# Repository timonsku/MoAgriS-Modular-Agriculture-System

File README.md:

# MoAgriS - Modular Agriculture System

## Introduction
MoAgriS is a System to automate plant care with the help of modules for light, water and wind. The modules are plugged onto 3 rods providing power and communication. This way they can be placed individually to fit the plants needs. The project has been developed under Windows but the use of Linux is possible and encouraged.

## Quickstart
There is none. You need to get the PCBs and the components of the [BOM](#bom) first and combine them yourself or let your provider populate everything. [LCSC](https://lcsc.com/) has been quite usefull since they offer a [PCB service](https://jlcpcb.com/) besides the components and the shipment can be combined. A possible PCB configuration can be seen in [PCB/notes/pcb-spec.PNG](./PCB/notes/pcb-spec.PNG). The default values such as PCB thickness or copper weight of 1 oz are fine, too. Unfortunately not all parts can be found there at the time of writing such as the SAMD11 or the PT4115 current regulator.

Once a PCB is ready the SAMD11 needs a [bootloader](https://github.com/mattairtech/ArduinoCore-samd/blob/master/bootloaders/zero/binaries/sam_ba_Generic_D11C14A_SAMD11C14A.bin) by [Mattairtech](https://github.com/mattairtech) to be transmitted via the SWD interface. This is a one-time procedure since the bootloader handles all the firmware updates via USB afterwards. The [Segger J-Link](https://www.segger.com/products/debug-probes/j-link/models/j-link-edu-mini/) comes in handy for that if the licensing is not a problem to you. Other solutions are possible as long as the SAMD11 is supported. Currently I use [Atmel Studio](https://www.microchip.com/mplab/avr-support/atmel-studio-7) for this step (Tools->Device Programming) though the Studio is quite an overkill.

Right now there is no Firmware binary (see [Future](#Future)) so you need to go through the [Development](#Development) section to set up the [Arduino IDE](https://www.arduino.cc/en/main/software). After that you can compile and upload the firmwares found in [Firmware](/Firmware). You need one master on the SDI bus and you can use pretty much as many slaves as you want - tell me if there's a limit. The master can be any PCB that has a SAMD11 if you wish to wish keep your order small. The dedicated master PCB only has power and BUS connectors.

Now that the PCBs are fully working it's time to clamp them on the rods. Plug the master via USB into your PC/Raspberry and open a serial console such as Realterm (Windows) or minicom (Linux). Find out the masters COM-Port (Windows: Device Manager -> COM & LPT ports -> the one thats containing Mattairtech in the description), set the Baud rate to 115200 and connect to it. You should receive a welcoming "Opening SDI-12 bus master..." the first time you connect to the master. It's best to tell your terminal to add a line feed (\n) to a command. This way the master knows to send it over the SDI bus - it's not neccessary since a command is sent anyway after a timeout of 1s.

That's it pretty much. You should be able to send commands to the individual modules now. There's a node-red solution in development to automate it further.

## Development
Thanks to [Mattairtechs ArduinoCore-samd](https://github.com/mattairtech/ArduinoCore-samd) firmware development is quite easy. The setup is described [here](https://github.com/mattairtech/ArduinoCore-samd#installation) (two parts!). The flash size of the SAMD11 is quite small to fit in all the firmware but it is possible if you turn off as many functions as possible in the config.h (Windows: C:\Users\User\AppData\Local\Arduino15\packages\MattairTech_Arduino\hardware\samd\1.6.18-beta-b1\config.h). My config can be found in [Firmware/config.h](./Firmware/config.h). Additionally you should avoid costful code such as the String datatype. Right now the complete firmware for the slave takes up 10232 Bytes.

## SDI Commands
The SDI protocol consists of commands from the master and answers from the sensors in printable 7bit ACII characters. A command starts with an [address](#Addressing) followed by an instruction and an optional parameter. It is finished with an '!' and sent to the module(s). If the command is a heartbeat or a group instruction the module doesn't answer. If a certain module is addressed the answer will be given via the SDI bus starting with its address and an answer. That string is also printed to the serial if you connected the module via USB for debugging purposes.

### Addressing
The modules are addressed by a 4 character lower case hex string which represents two bytes of an SDI address. It is created during bootup in the module by xoring the 3 serial number registers of the SAMD11. Since there is no EEPROM on the controller this seems to be the best solution for getting almost unique addresses. When you install the firmware you should set up a one master one slave system to get the modules address by '?I!' and write it somewhere like the left out rectangle on the module.

Besides addressing a single module you can address multiple ones with a single command. That way you won't receive an answer though. The wildcard character '?' will address all modules. If an single upper case letter is used you can address groups. The default group is 'N' as in None. You can set the group of a module by sending 'abcdGL!' ('abcd' = address, 'G' = set group, 'L' = Group L). Remember there is no EEPROM so the group will be lost once the module reboots. Either write a setup routine or set SDIGROUPDEFAULT in the firmware code to keep the group after booting.

### Instructions
Commands should be finished with \n and responses are finished by \r\n by the module itself.

| Instruction | Description | Answer | Example (Command!Response) |
| ----------- | ----------- | ------ | -------------------------- |
| I | Identification | abcd | ?I!abcd |
|||(Address)||
| V | Version | 00.00.02 | abcdV!abcd00.00.02 |
|||(Version)||
| Ccccc | Change address | [new Address] | abcdC1234!1234 |
|| cccc: Address |||
| H | Send Heartbeat to avoid module returning to a save state| - | ?H! |
| Jiiii | Set heartbeat interval | ACK | abcdJ0060!abcdACK |
|| iiii .. Interval in seconds (trailing 0s)
| Gc | Set SDI group | ACK | abcdGL!abcdACK
|| c: Group
| K | Get SDI group | [Group] | abcdK!abcdL
| Si | Set status LED | ACK | abcdS0!abcdACK
|| i: 0 (on), 1 (off) 
| Liii | Set power LED | ACK | abcdL100!abcdACK
|| iii: 000..255 (trailing 0s) || LL255!
| Pi | Set pump | ACK | abcdP1
|| i: 1(on), 0(off)
| Fiii | Set fan | ACK | abcdF100!abcdACK
|| iii: 000..255 (trailing 0s)

## BOM
The [BOM /PCB/notes/BOM.ods](./PCB/notes/BOM.ods) is divided into the BaseBoard which contains the components all modules share except for the Angle. Since some more parts of the BaseBoard are required for certain modules the column "See also" tells you where to look. 
There is also a [Accessories /PCB/notes/Accessories.ods](./PCB/notes/Accessories.ods) list to find some ideas about the other utensils.

## Modules
All modules are created in [Eagle](https://www.autodesk.com/products/eagle/overview) and are within the 10cm*10cm limit to use the free version.

### LED-Module 
Provides light by 3 full spectrum LEDs which intensity can be controlled via SDI. The long version has a better light and heat distribution.

### Pump-Module 
Provides water by a pump by switching it on/off via SDI. 

### Fan-Module
Provides wind by a fan that can be controlled via PWM over SDI. 

### SDI-Master
Optional board to be used as a SDI master. You can use any other module as a master but this one is optimized for the job. It is as slim as the LED PCB and has two possible power connectors - only use one. The screw connector also has a third terminal to also chain the BUS signal.

### Angle
Provides an ~90° angle for the rods. 

## Future
More things could be added such as
- Sensors: Currently a LED-Board is technically capable of driving sensors since all pins are routed outside:
	- Watering could depend on the wetness of the soil
	- Measure the water level of the pump tank to send an alert to refill
- Create a node-red configuration
- Find an alternative to Atmel Studio for installing the bootloader
- Provide firmware binaries to avoid setting up Arduino IDE

## Bugs
- Modules don't answer after hours of no use
- Sometimes there's a voltage on the BUS of 0.1-2.5V
- Sometimes the BUS only works when a logic analyzer is attached to GND/BUS

## More
<br />This work is licensed under a <a rel="license" href="http://creativecommons.org/licenses/by-sa/4.0/">Creative Commons Attribution-ShareAlike 4.0 International License</a>.

For more details see https://hackaday.io/project/91757-moagris-modular-agriculture-system

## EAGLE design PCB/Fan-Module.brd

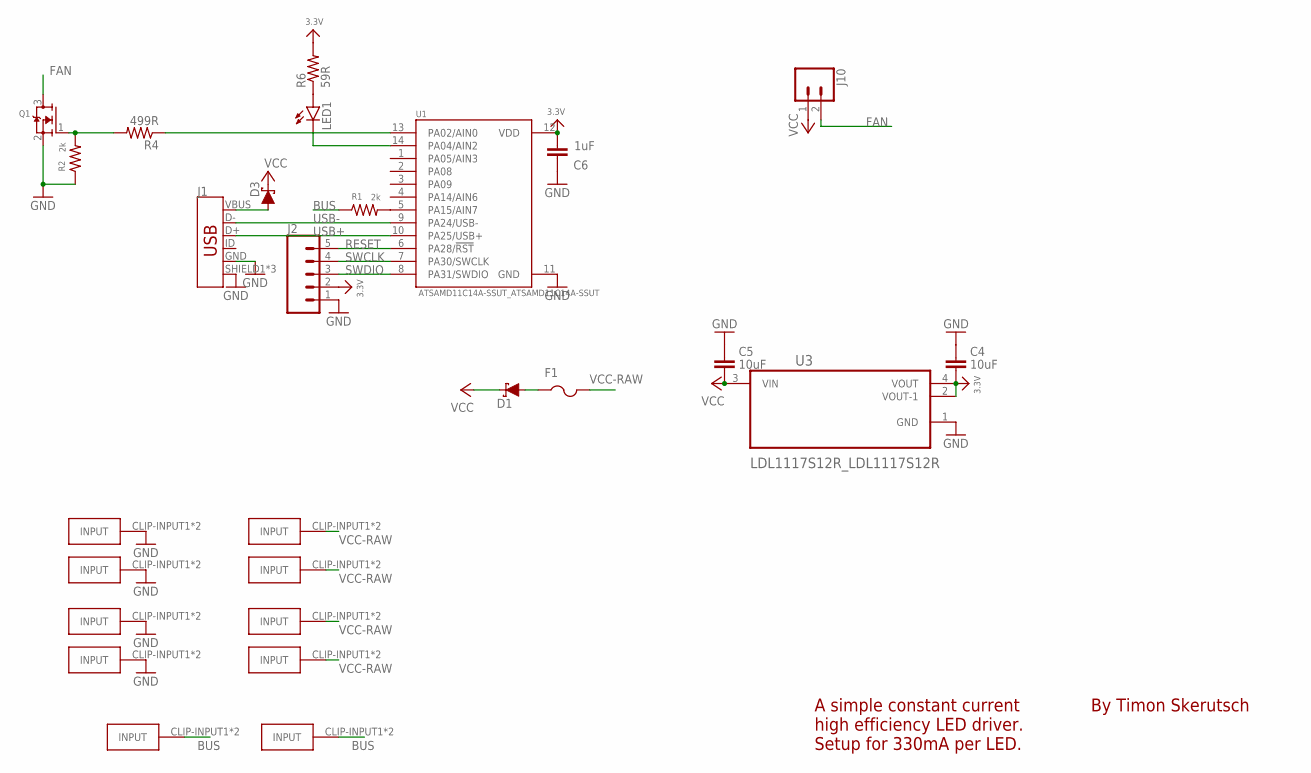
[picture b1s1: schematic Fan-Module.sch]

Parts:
C4, C5: 10uF; C0603
C6: 1uF; C0603
D1, D3: 3A/40V/500mV; SMA-DIODE
F1: PTCFUSE-1812; 1812
GND-CLIP, GND-CLIP1, GND-CLIP2, GND-CLIP3: FUSE-HOLDER-5X20MM
J1: USB_MICRO-B_FEMALE-SMT; USB-B-MICRO-SMD
J2: CONN_05; 1X05
J10: CONN_02PTH3; 1X02_LONGPADS
LED1: LEDCHIPLED_0805; CHIPLED_0805
PWM-CLIP, PWM-CLIP1: FUSE-HOLDER-5X20MM
Q1: MOSFET-NWIDE; SOT23-WIDE
R1, R2: 2k; R1206
R4: 499R; R0805
R6: 59R; R0805
U1: ATSAMD11C14A-SSUT_ATSAMD11C14A-SSUT; ATSAMD11C14A-SSUT_SOIC127P600X160-14N
U3: LDL1117S12R_LDL1117S12R; LDL1117S12R_SOT230P700X180-4N
VCC-CLIP, VCC-CLIP1, VCC-CLIP2, VCC-CLIP3: FUSE-HOLDER-5X20MM

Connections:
3.3V: C4.2, C6.2, J2.2, R6.2, U1.12 (VDD), U3.2 (VOUT-1), U3.4 (VOUT)
BUS: PWM-CLIP.CLIP-INPUT1, PWM-CLIP.CLIP-INPUT2, PWM-CLIP1.CLIP-INPUT1, PWM-CLIP1.CLIP-INPUT2, R1.1
FAN: J10.2, Q1.3 (D)
GND: C4.1, C5.1, C6.1, GND-CLIP.CLIP-INPUT1, GND-CLIP.CLIP-INPUT2, GND-CLIP1.CLIP-INPUT1, GND-CLIP1.CLIP-INPUT2, GND-CLIP2.CLIP-INPUT1, GND-CLIP2.CLIP-INPUT2, GND-CLIP3.CLIP-INPUT1, GND-CLIP3.CLIP-INPUT2, J1.GND, J1.SHIELD1 (SHIELD), J1.SHIELD2 (SHIELD), J1.SHIELD3 (SHIELD), J2.1, Q1.2 (S), R2.1, U1.11 (GND), U3.1 (GND)
unnamed: LED1.C, U1.14 (PA04/AIN2)
unnamed: LED1.A, R6.1
unnamed: R1.2, U1.5 (PA15/AIN7)
unnamed: D3.A, J1.VBUS
unnamed: R4.1, U1.13 (PA02/AIN0)
unnamed: D1.A, F1.1
unnamed: Q1.1 (G), R2.2, R4.2
RESET: J2.5, U1.6 (PA28/!RST)
SWCLK: J2.4, U1.7 (PA30/SWCLK)
SWDIO: J2.3, U1.8 (PA31/SWDIO)
USB+: J1.D+, U1.10 (PA25/USB+)
USB-: J1.D-, U1.9 (PA24/USB-)
VCC: C5.2, D1.C, D3.C, J10.1, U3.3 (VIN)
VCC-RAW: F1.2, VCC-CLIP.CLIP-INPUT1, VCC-CLIP.CLIP-INPUT2, VCC-CLIP1.CLIP-INPUT1, VCC-CLIP1.CLIP-INPUT2, VCC-CLIP2.CLIP-INPUT1, VCC-CLIP2.CLIP-INPUT2, VCC-CLIP3.CLIP-INPUT1, VCC-CLIP3.CLIP-INPUT2

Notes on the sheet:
By Timon Skerutsch
A simple constant current high efficiency LED driver. Setup for 330mA per LED.

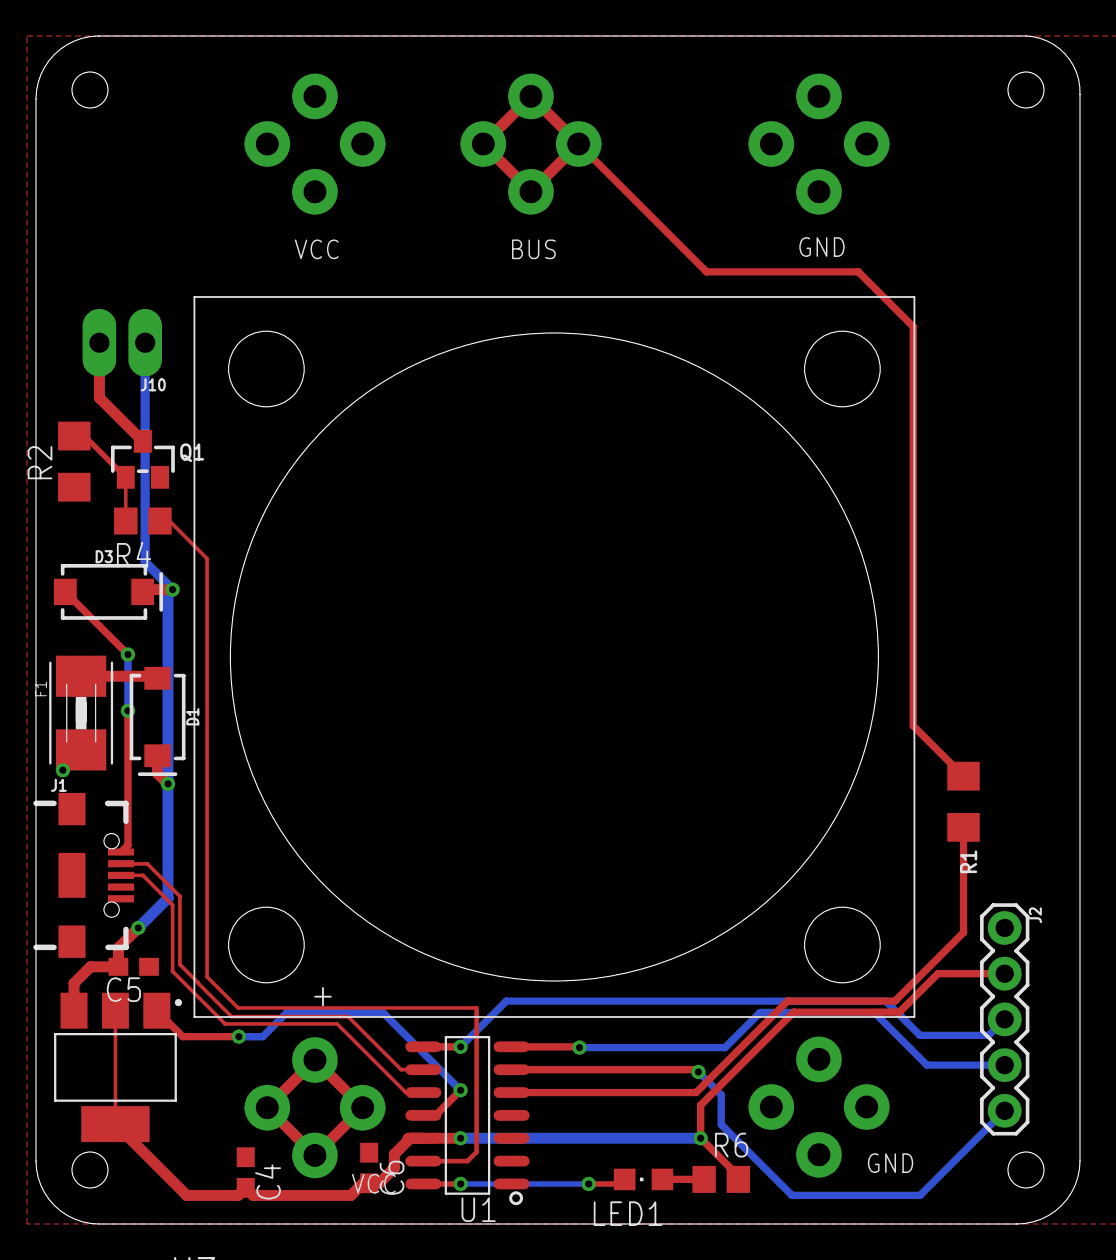
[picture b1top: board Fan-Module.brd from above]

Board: 2 copper layers, 58.0 x 66.0 mm, 28 parts (1 on the bottom side), 18 nets.

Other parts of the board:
U$1: 40MM-FAN

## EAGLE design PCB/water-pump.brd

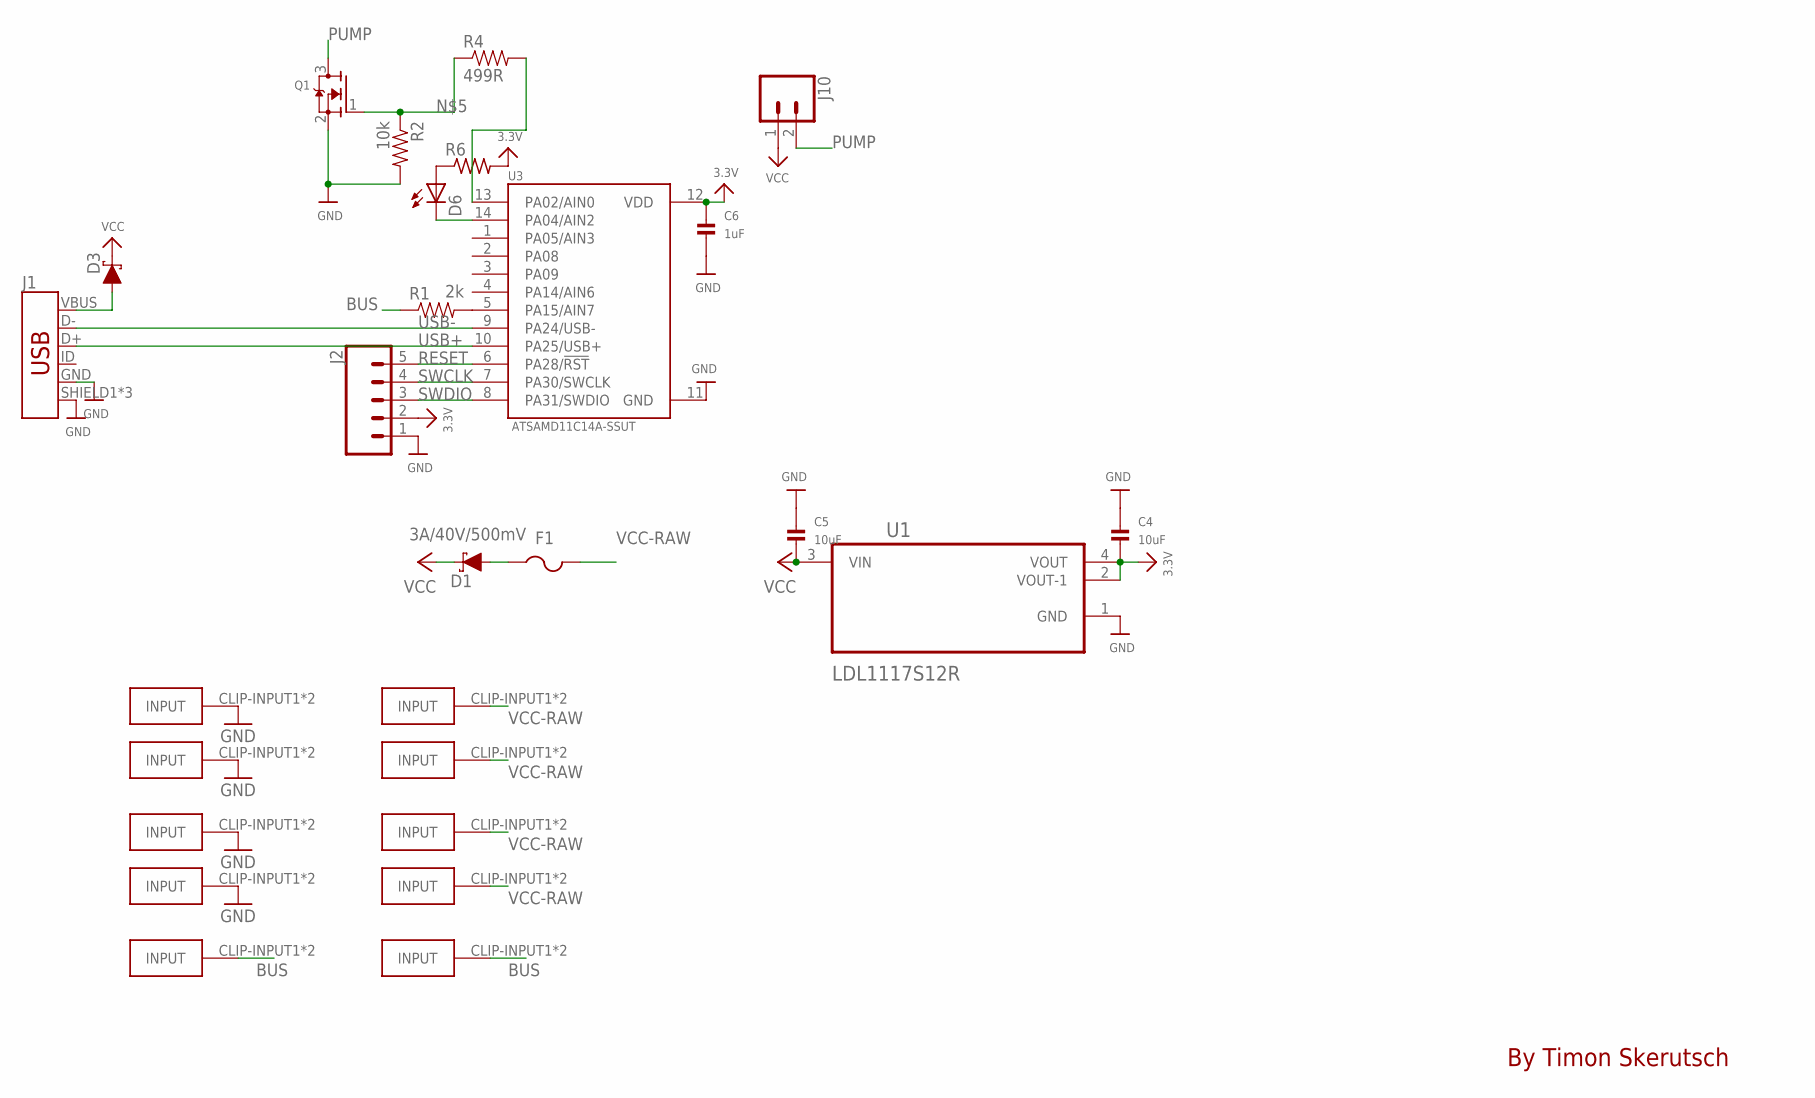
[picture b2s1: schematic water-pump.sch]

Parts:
C4, C5: 10uF; 0805
C6: 1uF; 0603
D1, D3: 3A/40V/500mV; SMA-DIODE
D6: LEDCHIPLED_0805; CHIPLED_0805
F1: PTCFUSE-1812; 1812
GND-CLIP, GND-CLIP1, GND-CLIP2, GND-CLIP3: FUSE-HOLDER-5X20MM
J1: USB_MICRO-B_FEMALE-SMT; USB-B-MICRO-SMD
J2: CONN_05; 1X05
J10: CONN_02PTH3; 1X02_LONGPADS
PWM-CLIP, PWM-CLIP1: FUSE-HOLDER-5X20MM
Q1: MOSFET-NWIDE; SOT23-WIDE
R1: 2k; 1206
R2: 10k; 1206
R4: 499R; 1206
R6: R-US_R0805; R0805
U1: LDL1117S12R; SOT230P700X180-4N
U3: ATSAMD11C14A-SSUT; SOIC127P600X160-14N
VCC-CLIP, VCC-CLIP1, VCC-CLIP2, VCC-CLIP3: FUSE-HOLDER-5X20MM

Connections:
3.3V: C4.2, C6.1, J2.2, R6.2, U1.2 (VOUT-1), U1.4 (VOUT), U3.12 (VDD)
BUS: PWM-CLIP.CLIP-INPUT1, PWM-CLIP.CLIP-INPUT2, PWM-CLIP1.CLIP-INPUT1, PWM-CLIP1.CLIP-INPUT2, R1.1
GND: C4.1, C5.1, C6.2, GND-CLIP.CLIP-INPUT1, GND-CLIP.CLIP-INPUT2, GND-CLIP1.CLIP-INPUT1, GND-CLIP1.CLIP-INPUT2, GND-CLIP2.CLIP-INPUT1, GND-CLIP2.CLIP-INPUT2, GND-CLIP3.CLIP-INPUT1, GND-CLIP3.CLIP-INPUT2, J1.GND, J1.SHIELD1 (SHIELD), J1.SHIELD2 (SHIELD), J1.SHIELD3 (SHIELD), J2.1, Q1.2 (S), R2.2, U1.1 (GND), U3.11 (GND)
unnamed: D3.A, J1.VBUS
unnamed: R1.2, U3.5 (PA15/AIN7)
unnamed: Q1.1 (G), R2.1, R4.1
unnamed: D1.A, F1.1
unnamed: D6.A, R6.1
unnamed: D6.C, U3.14 (PA04/AIN2)
PUMP: J10.2, Q1.3 (D)
PUMP_CTRL: R4.2, U3.13 (PA02/AIN0)
RESET: J2.5, U3.6 (PA28/!RST)
SWCLK: J2.4, U3.7 (PA30/SWCLK)
SWDIO: J2.3, U3.8 (PA31/SWDIO)
USB+: J1.D+, U3.10 (PA25/USB+)
USB-: J1.D-, U3.9 (PA24/USB-)
VCC: C5.2, D1.C, D3.C, J10.1, U1.3 (VIN)
VCC-RAW: F1.2, VCC-CLIP.CLIP-INPUT1, VCC-CLIP.CLIP-INPUT2, VCC-CLIP1.CLIP-INPUT1, VCC-CLIP1.CLIP-INPUT2, VCC-CLIP2.CLIP-INPUT1, VCC-CLIP2.CLIP-INPUT2, VCC-CLIP3.CLIP-INPUT1, VCC-CLIP3.CLIP-INPUT2

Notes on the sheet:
By Timon Skerutsch

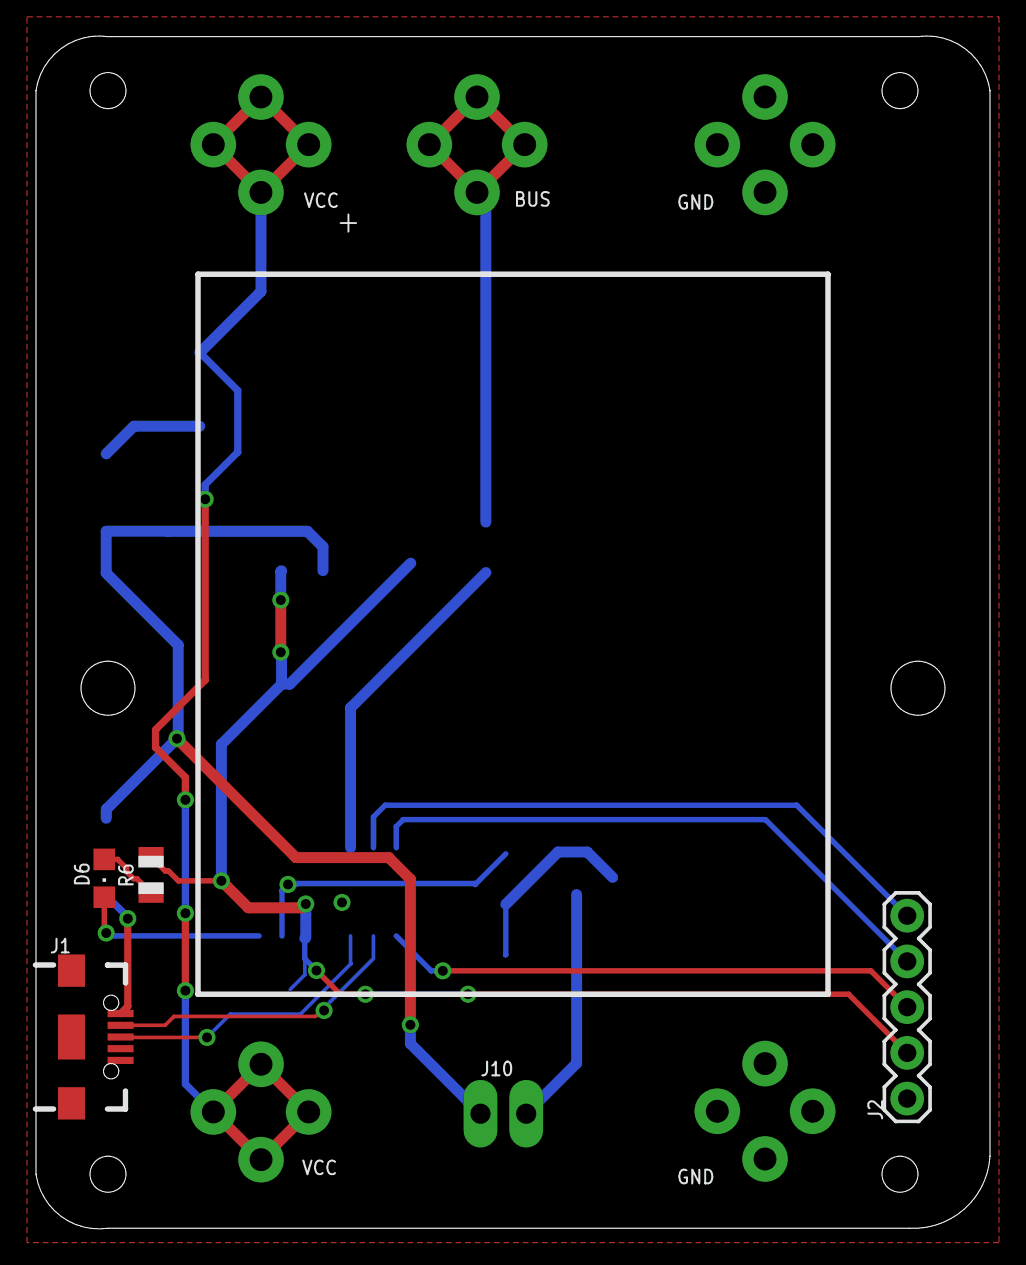
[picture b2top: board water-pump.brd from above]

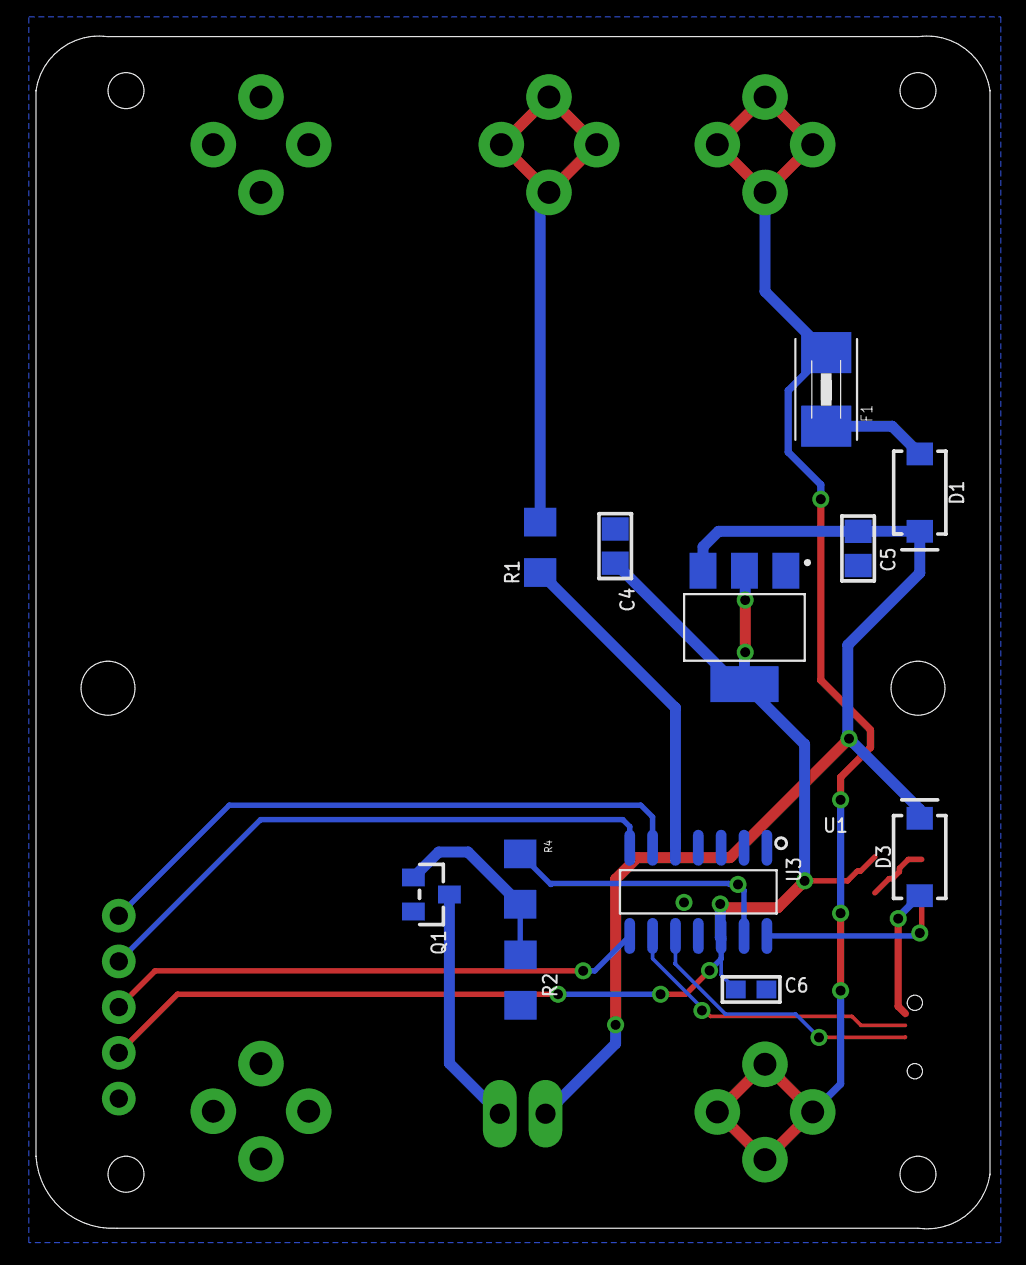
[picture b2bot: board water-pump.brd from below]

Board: 2 copper layers, 53.0 x 66.3 mm, 27 parts (22 on the bottom side), 18 nets.

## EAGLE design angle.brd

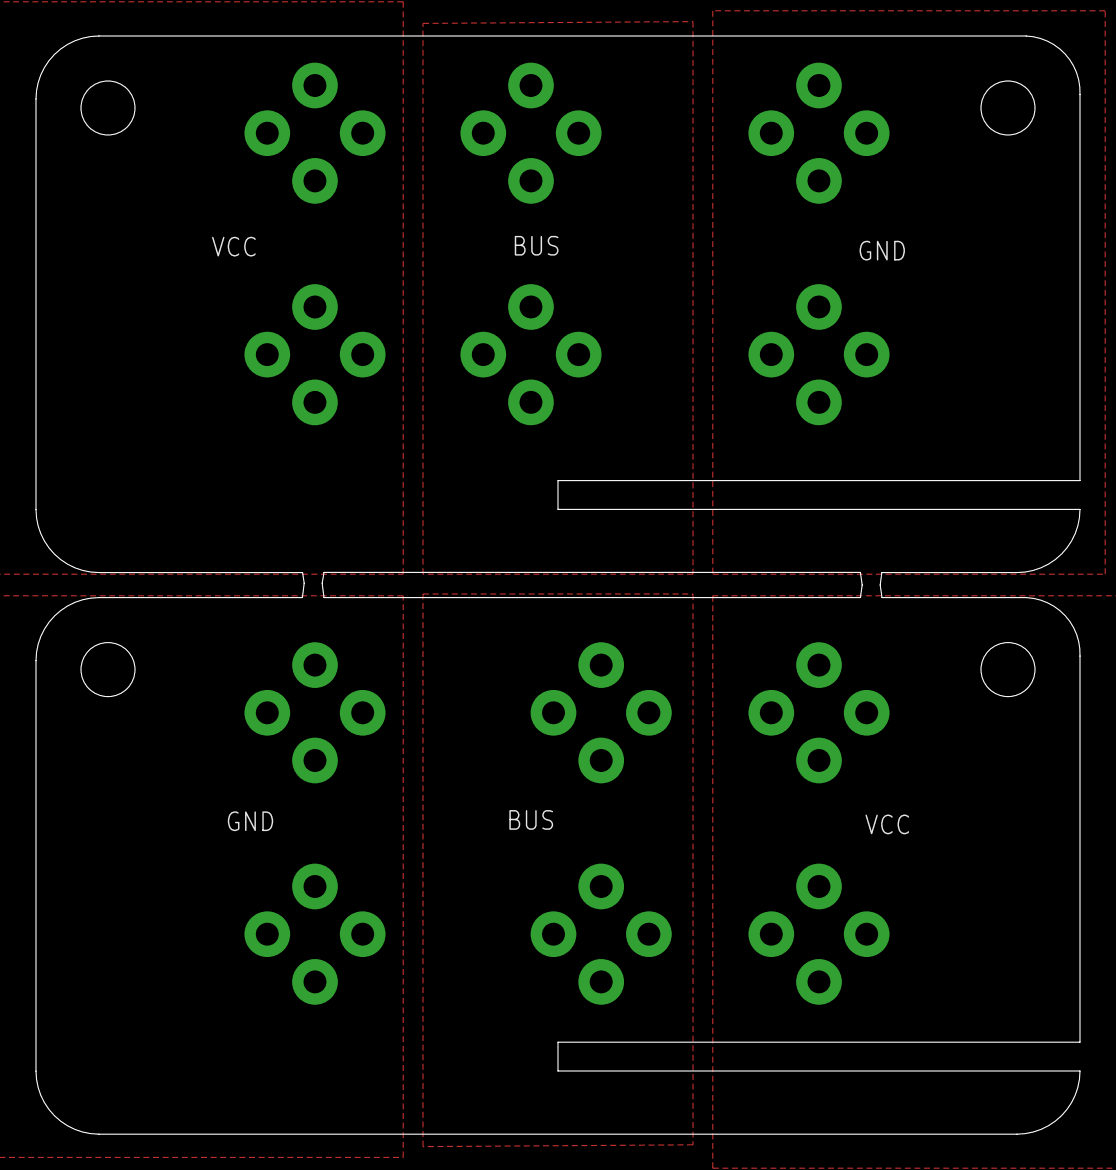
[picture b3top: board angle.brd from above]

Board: 2 copper layers, 58.0 x 61.0 mm, 24 parts (1 on the bottom side), 6 nets, no tracks yet.

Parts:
ABUS-CLIP, ABUS-CLIP1, ABUS-CLIP2, ABUS-CLIP3: FUSE-HOLDER-5X20MM
AGND-CLIP, AGND-CLIP1, AGND-CLIP2, AGND-CLIP3: FUSE-HOLDER-5X20MM
AVCC-CLIP, AVCC-CLIP1, AVCC-CLIP2, AVCC-CLIP3: FUSE-HOLDER-5X20MM
BBUS-CLIP, BBUS-CLIP1, BBUS-CLIP2, BBUS-CLIP3: FUSE-HOLDER-5X20MM
BGND-CLIP, BGND-CLIP1, BGND-CLIP2, BGND-CLIP3: FUSE-HOLDER-5X20MM
BVCC-CLIP, BVCC-CLIP1, BVCC-CLIP2, BVCC-CLIP3: FUSE-HOLDER-5X20MM

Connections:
ABUS: ABUS-CLIP.CLIP-INPUT1, ABUS-CLIP.CLIP-INPUT2, ABUS-CLIP1.CLIP-INPUT1, ABUS-CLIP1.CLIP-INPUT2, ABUS-CLIP2.CLIP-INPUT1, ABUS-CLIP2.CLIP-INPUT2, ABUS-CLIP3.CLIP-INPUT1, ABUS-CLIP3.CLIP-INPUT2
AGND: AGND-CLIP.CLIP-INPUT1, AGND-CLIP.CLIP-INPUT2, AGND-CLIP1.CLIP-INPUT1, AGND-CLIP1.CLIP-INPUT2, AGND-CLIP2.CLIP-INPUT1, AGND-CLIP2.CLIP-INPUT2, AGND-CLIP3.CLIP-INPUT1, AGND-CLIP3.CLIP-INPUT2
AVCC-RAW: AVCC-CLIP.CLIP-INPUT1, AVCC-CLIP.CLIP-INPUT2, AVCC-CLIP1.CLIP-INPUT1, AVCC-CLIP1.CLIP-INPUT2, AVCC-CLIP2.CLIP-INPUT1, AVCC-CLIP2.CLIP-INPUT2, AVCC-CLIP3.CLIP-INPUT1, AVCC-CLIP3.CLIP-INPUT2
BBUS: BBUS-CLIP.CLIP-INPUT1, BBUS-CLIP.CLIP-INPUT2, BBUS-CLIP1.CLIP-INPUT1, BBUS-CLIP1.CLIP-INPUT2, BBUS-CLIP2.CLIP-INPUT1, BBUS-CLIP2.CLIP-INPUT2, BBUS-CLIP3.CLIP-INPUT1, BBUS-CLIP3.CLIP-INPUT2
BGND: BGND-CLIP.CLIP-INPUT1, BGND-CLIP.CLIP-INPUT2, BGND-CLIP1.CLIP-INPUT1, BGND-CLIP1.CLIP-INPUT2, BGND-CLIP2.CLIP-INPUT1, BGND-CLIP2.CLIP-INPUT2, BGND-CLIP3.CLIP-INPUT1, BGND-CLIP3.CLIP-INPUT2
BVCC-RAW: BVCC-CLIP.CLIP-INPUT1, BVCC-CLIP.CLIP-INPUT2, BVCC-CLIP1.CLIP-INPUT1, BVCC-CLIP1.CLIP-INPUT2, BVCC-CLIP2.CLIP-INPUT1, BVCC-CLIP2.CLIP-INPUT2, BVCC-CLIP3.CLIP-INPUT1, BVCC-CLIP3.CLIP-INPUT2

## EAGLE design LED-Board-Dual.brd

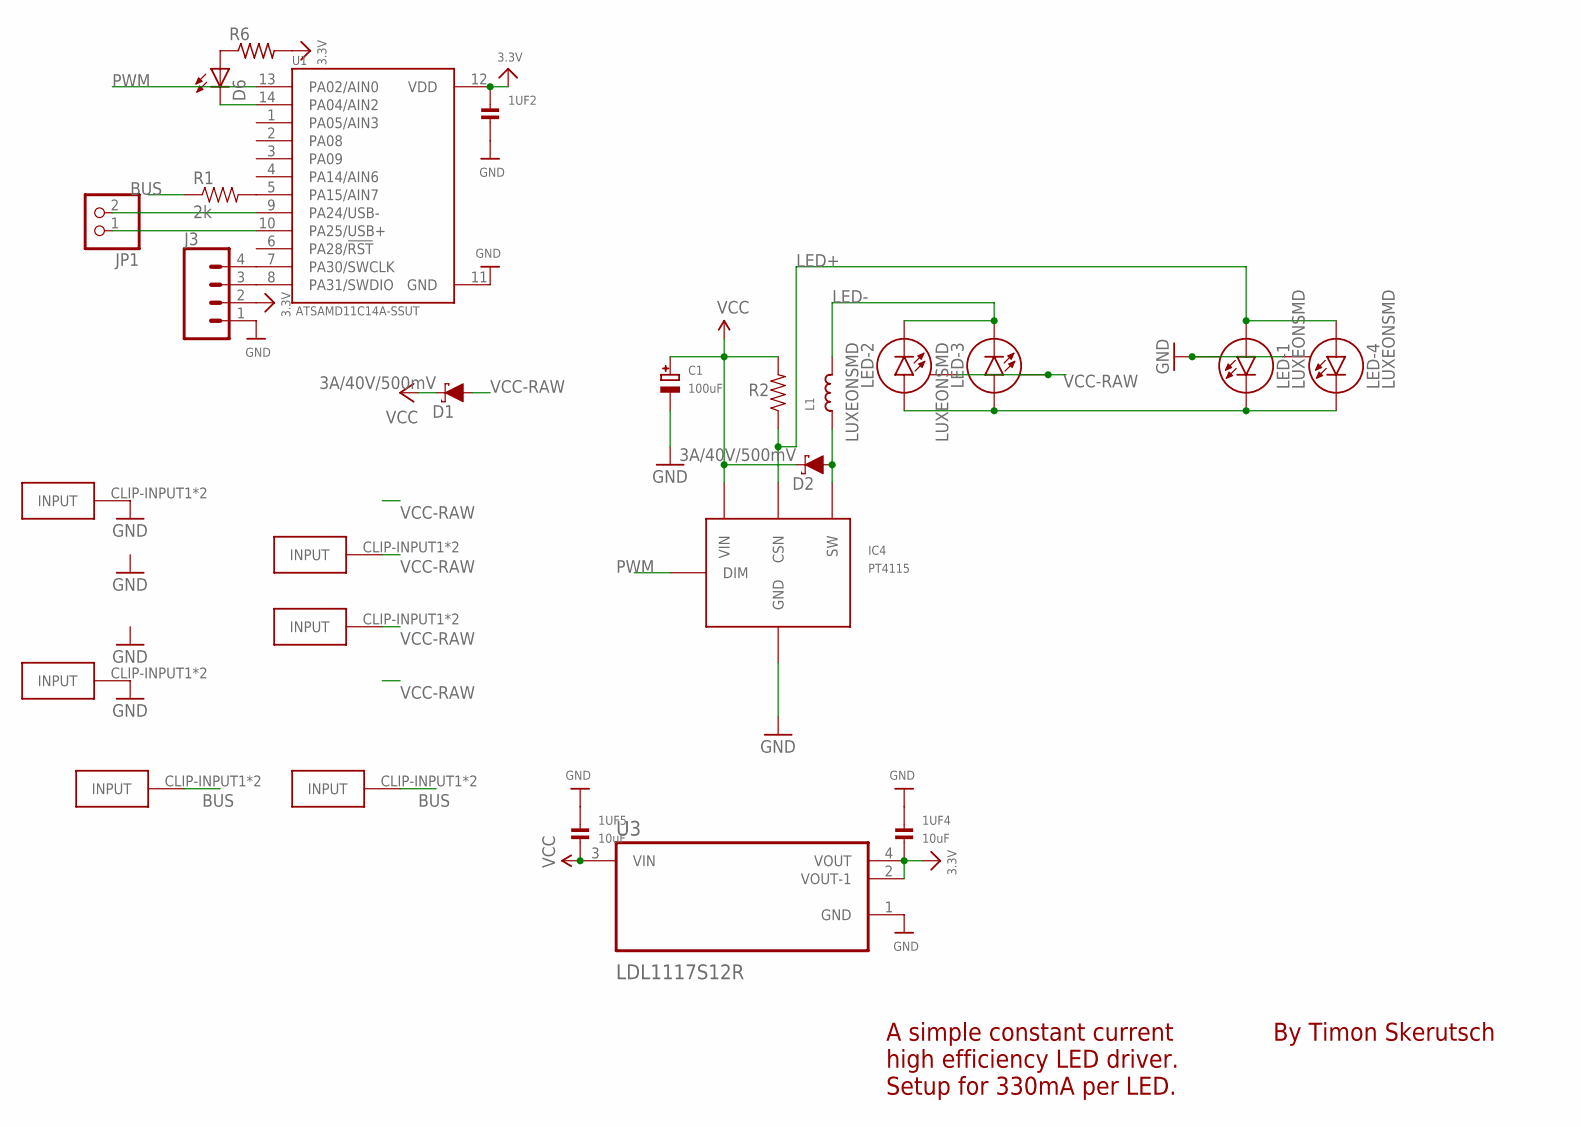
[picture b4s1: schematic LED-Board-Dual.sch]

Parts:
1UF2: CAP_CERAMIC0603; 0603
1UF4, 1UF5: 10uF; 0805
C1: 100uF; PANASONIC_C
D1, D2: 3A/40V/500mV; SMA-DIODE
D6: LEDCHIPLED_0805; CHIPLED_0805
GND-CLIP, GND-CLIP3: FUSE-HOLDER-5X20MM
IC4: PT4115
J3: CONN_04; 1X04
JP1: HEADER-1X2; 1X02_OVAL
L1: INDUCTORTDK_VLC6045; INDUCTOR_6X6MM_TDK_VLC6045
LED-1, LED-2, LED-3, LED-4: LUXEONSMD; LUXEON
PWM-CLIP, PWM-CLIP1: FUSE-HOLDER-5X20MM
R1: 2k; 1206
R2: 0.3; 1206
R6: R-US_R0805; R0805
U1: ATSAMD11C14A-SSUT; SOIC127P600X160-14N
U3: LDL1117S12R; SOT230P700X180-4N
VCC-CLIP, VCC-CLIP3: FUSE-HOLDER-5X20MM

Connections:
3.3V: 1UF2.1, 1UF4.2, J3.2, R6.2, U1.12 (VDD), U3.2 (VOUT-1), U3.4 (VOUT)
BUS: PWM-CLIP.CLIP-INPUT1, PWM-CLIP.CLIP-INPUT2, PWM-CLIP1.CLIP-INPUT1, PWM-CLIP1.CLIP-INPUT2, R1.1
GND: C1.-, GND-CLIP.CLIP-INPUT1, GND-CLIP.CLIP-INPUT2, GND-CLIP3.CLIP-INPUT1, GND-CLIP3.CLIP-INPUT2, IC4.2 (GND), IC4.2A (GND), J3.1, LED-1.S, LED-4.S
GND2: U1.11 (GND)
GND3: U3.1 (GND)
LED+: IC4.4 (CSN), LED-1.A, LED-4.A, R2.1
LED-: L1.P$2 (2), LED-2.C, LED-3.C
unnamed: D2.A, IC4.1 (SW), L1.P$1 (1)
unnamed: LED-1.C, LED-2.A, LED-3.A, LED-4.C
unnamed: J3.3, U1.8 (PA31/SWDIO)
unnamed: J3.4, U1.7 (PA30/SWCLK)
unnamed: R1.2, U1.5 (PA15/AIN7)
unnamed: D6.A, R6.1
unnamed: JP1.1, U1.10 (PA25/USB+)
unnamed: JP1.2, U1.9 (PA24/USB-)
unnamed: D6.C, U1.14 (PA04/AIN2)
PWM: IC4.3 (DIM), U1.13 (PA02/AIN0)
VCC: 1UF5.2, C1.+, D1.C, D2.C, IC4.5 (VIN), R2.2, U3.3 (VIN)
VCC-RAW: D1.A, LED-2.S, LED-3.S, VCC-CLIP.CLIP-INPUT1, VCC-CLIP.CLIP-INPUT2, VCC-CLIP3.CLIP-INPUT1, VCC-CLIP3.CLIP-INPUT2

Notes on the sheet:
By Timon Skerutsch
A simple constant current high efficiency LED driver. Setup for 330mA per LED.

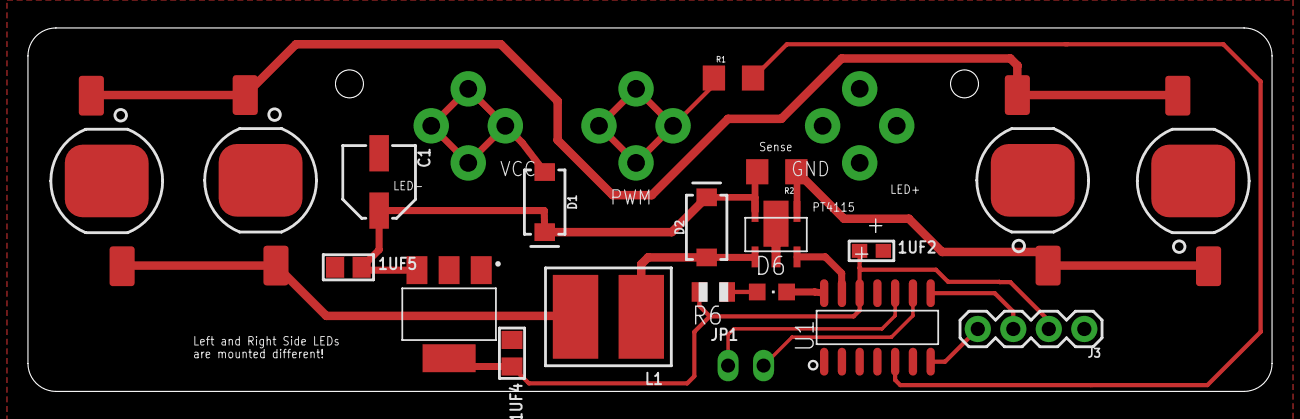
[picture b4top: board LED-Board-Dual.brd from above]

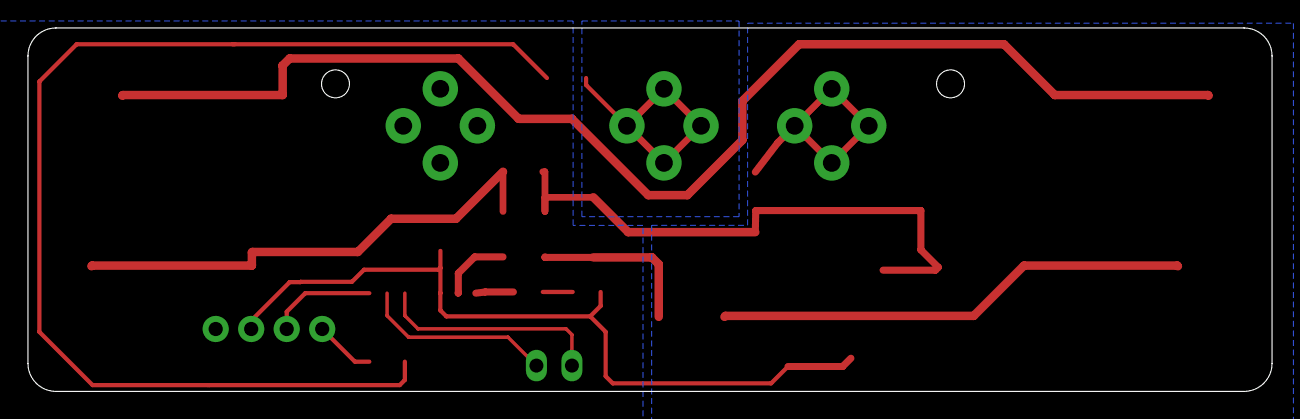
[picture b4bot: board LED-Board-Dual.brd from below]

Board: 2 copper layers, 89.0 x 26.0 mm, 26 parts (6 on the bottom side), 17 nets.

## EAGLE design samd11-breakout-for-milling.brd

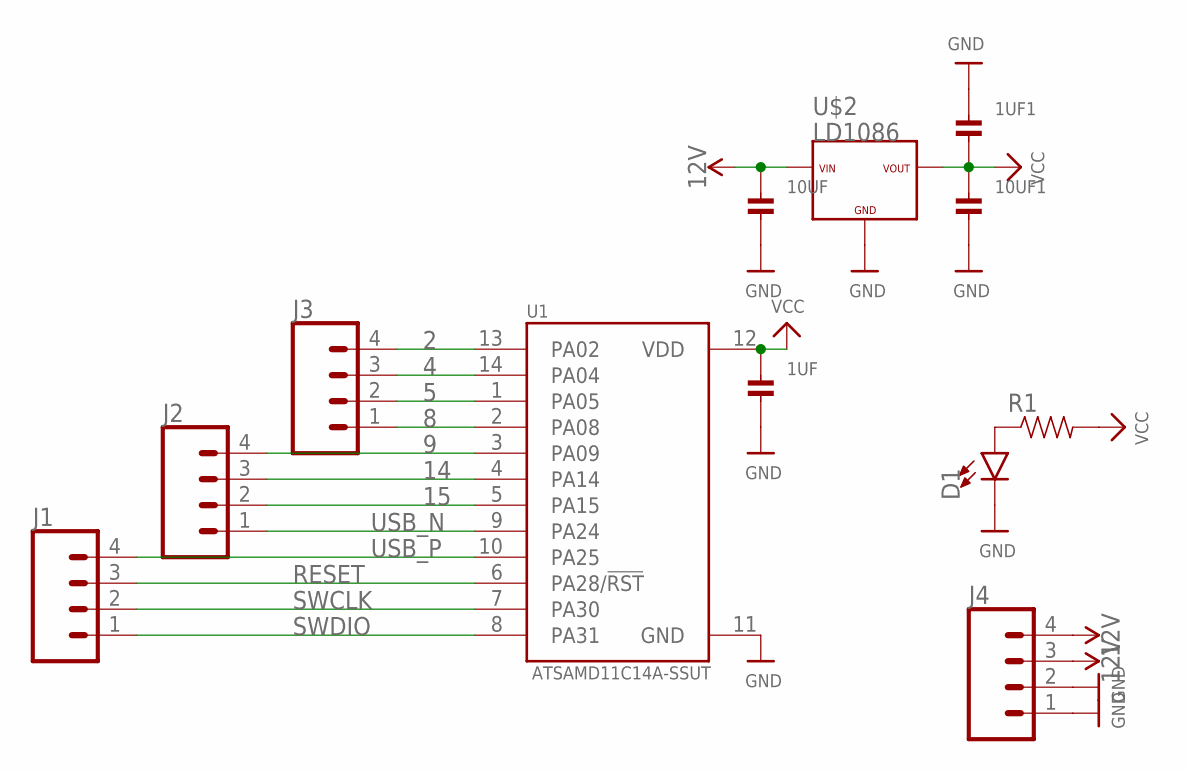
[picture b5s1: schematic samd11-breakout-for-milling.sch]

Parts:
1UF, 1UF1: CAP_CERAMIC0603; 0603
10UF, 10UF1: CAP_CERAMIC0805; 0805
D1: LED5MM-KIT; LED_5MM-KIT
J1, J2, J3, J4: CONN_04SMD_RA_FEMALE; 1X04_SMD_RA_FEMALE
R1: RESISTOR1206; 1206
U1: ATSAMD11C14A-SSUT; SOIC127P600X160-14N
U$2: LD1086; D2PAK

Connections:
2: J3.4, U1.13 (PA02)
4: J3.3, U1.14 (PA04)
5: J3.2, U1.1 (PA05)
8: J3.1, U1.2 (PA08)
9: J2.4, U1.3 (PA09)
12V: 10UF.1, J4.3, J4.4, U$2.VIN
14: J2.3, U1.4 (PA14)
15: J2.2, U1.5 (PA15)
GND: 1UF.2, 1UF1.1, 10UF.2, 10UF1.2, D1.K (C), J4.1, J4.2, U1.11 (GND), U$2.GND
unnamed: D1.A, R1.1
RESET: J1.3, U1.6 (PA28/!RST)
SWCLK: J1.2, U1.7 (PA30)
SWDIO: J1.1, U1.8 (PA31)
USB_N: J2.1, U1.9 (PA24)
USB_P: J1.4, U1.10 (PA25)
VCC: 1UF.1, 1UF1.2, 10UF1.1, R1.2, U1.12 (VDD), U$2.VOUT

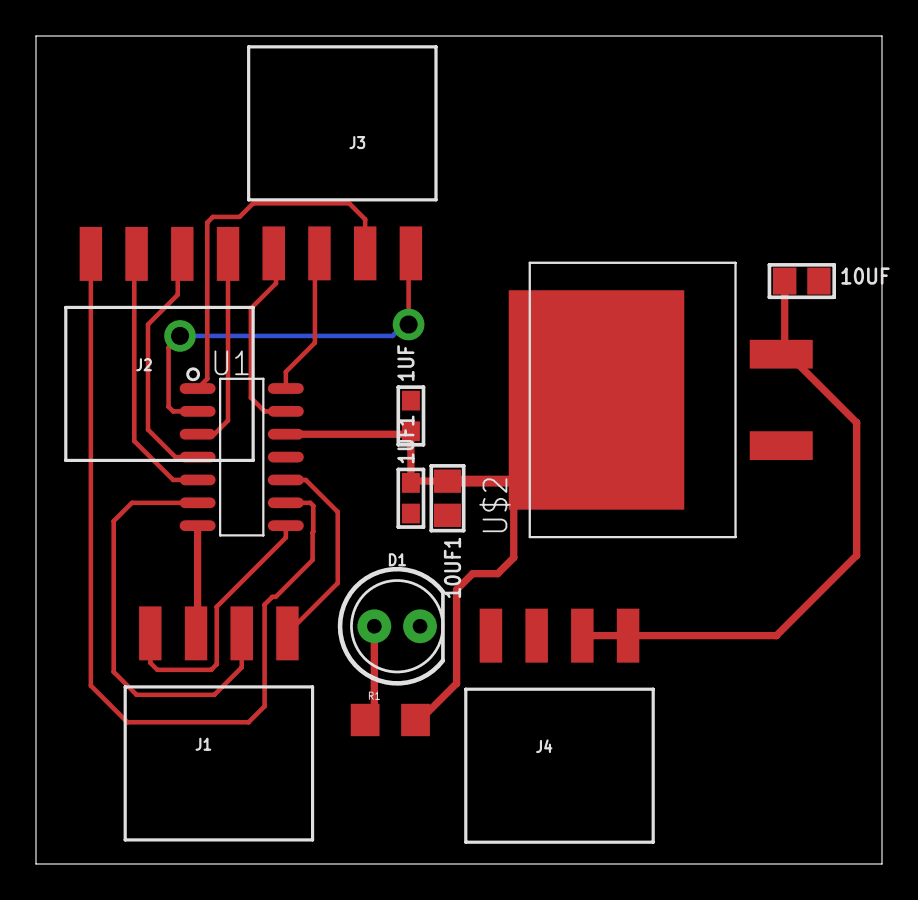
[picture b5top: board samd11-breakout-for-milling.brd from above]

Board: 2 copper layers, 47.0 x 46.0 mm, 12 parts (0 on the bottom side), 16 nets.

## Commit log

2018-04-20 PCB files
2018-04-20 Fusion 360 files
2019-01-27 Added fuse and reset pin breakout
2019-01-27 fixed up right angle
2019-01-27 applied .gitignore
2019-01-27 fixed polygons for angle, added gerber for angle
2019-02-03 fixed horrible git merge mistake
2019-02-04 final touches to LED board
2019-02-04 final final touch...
2019-02-04 fixing more horrible mistakes
2019-02-04 added lcsc part for fuse clip
2019-03-09 added values/aligned names and values
2019-03-10 exchanged j3 and c1/2 footprint of led module
2019-03-10 renamed some connectors
2019-03-10 added values
2019-03-10 added sdi functionality to fan module
2019-03-10 minor adjustments to water pump
2019-03-11 modified c6 to 1uF
2019-03-11 added firmware to repo
2019-03-11 added heartbeat, pump and powerled command; refactoring
2019-03-12 modified heartbeat and replaced string.toInt()
2019-03-12 doubled and mirrored angle pcb
2019-03-12 cleanup, (re)moved files
2019-03-13 added sdi-master pcb
2019-03-13 added button to pcbs and did some fixing
2019-03-14 modified firmware to use xored serialnumber, refactoring
2019-03-15 added missing resistor before mosfet
2019-03-15 setting safestate in master
2019-03-15 added config.h for mattair samd arduino core
2019-03-17 removed buttons.. not needed
2019-03-17 shrinked water pump pcb in length
2019-03-17 added bstop to led pads of led board
2019-03-17 added b/tstop and b/restricted to write address on pcb
2019-03-22 added power connectors to sdi master
2019-03-23 increased led board bottom polygons for more equal heatsinks
2019-03-25 added sdi-cmd version and removed test
2019-04-03 added group functions, settable heartbeattimer and debugged sdi communication
2019-04-03 added longer led board for better light and heat distribution
2019-04-06 cleaned up BOMs
2019-04-06 replaced 2 position terminal with 3 positions
2019-04-06 firmware cleanup
2019-04-06 added documentation in the readme
2019-04-07 little changes in readme

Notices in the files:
parts and their libraries:
SparkFun-Aesthetics: Licensing: Creative Commons ShareAlike 4.0 International - https://creativecommons.org/licenses/by-sa/4.0
microbuilder: This work is placed in the public domain, and may be freely used for commercial and non-commercial work with the following conditions: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
